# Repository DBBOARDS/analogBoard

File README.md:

# analogBoard
These are the Eagle files for the Analog Board

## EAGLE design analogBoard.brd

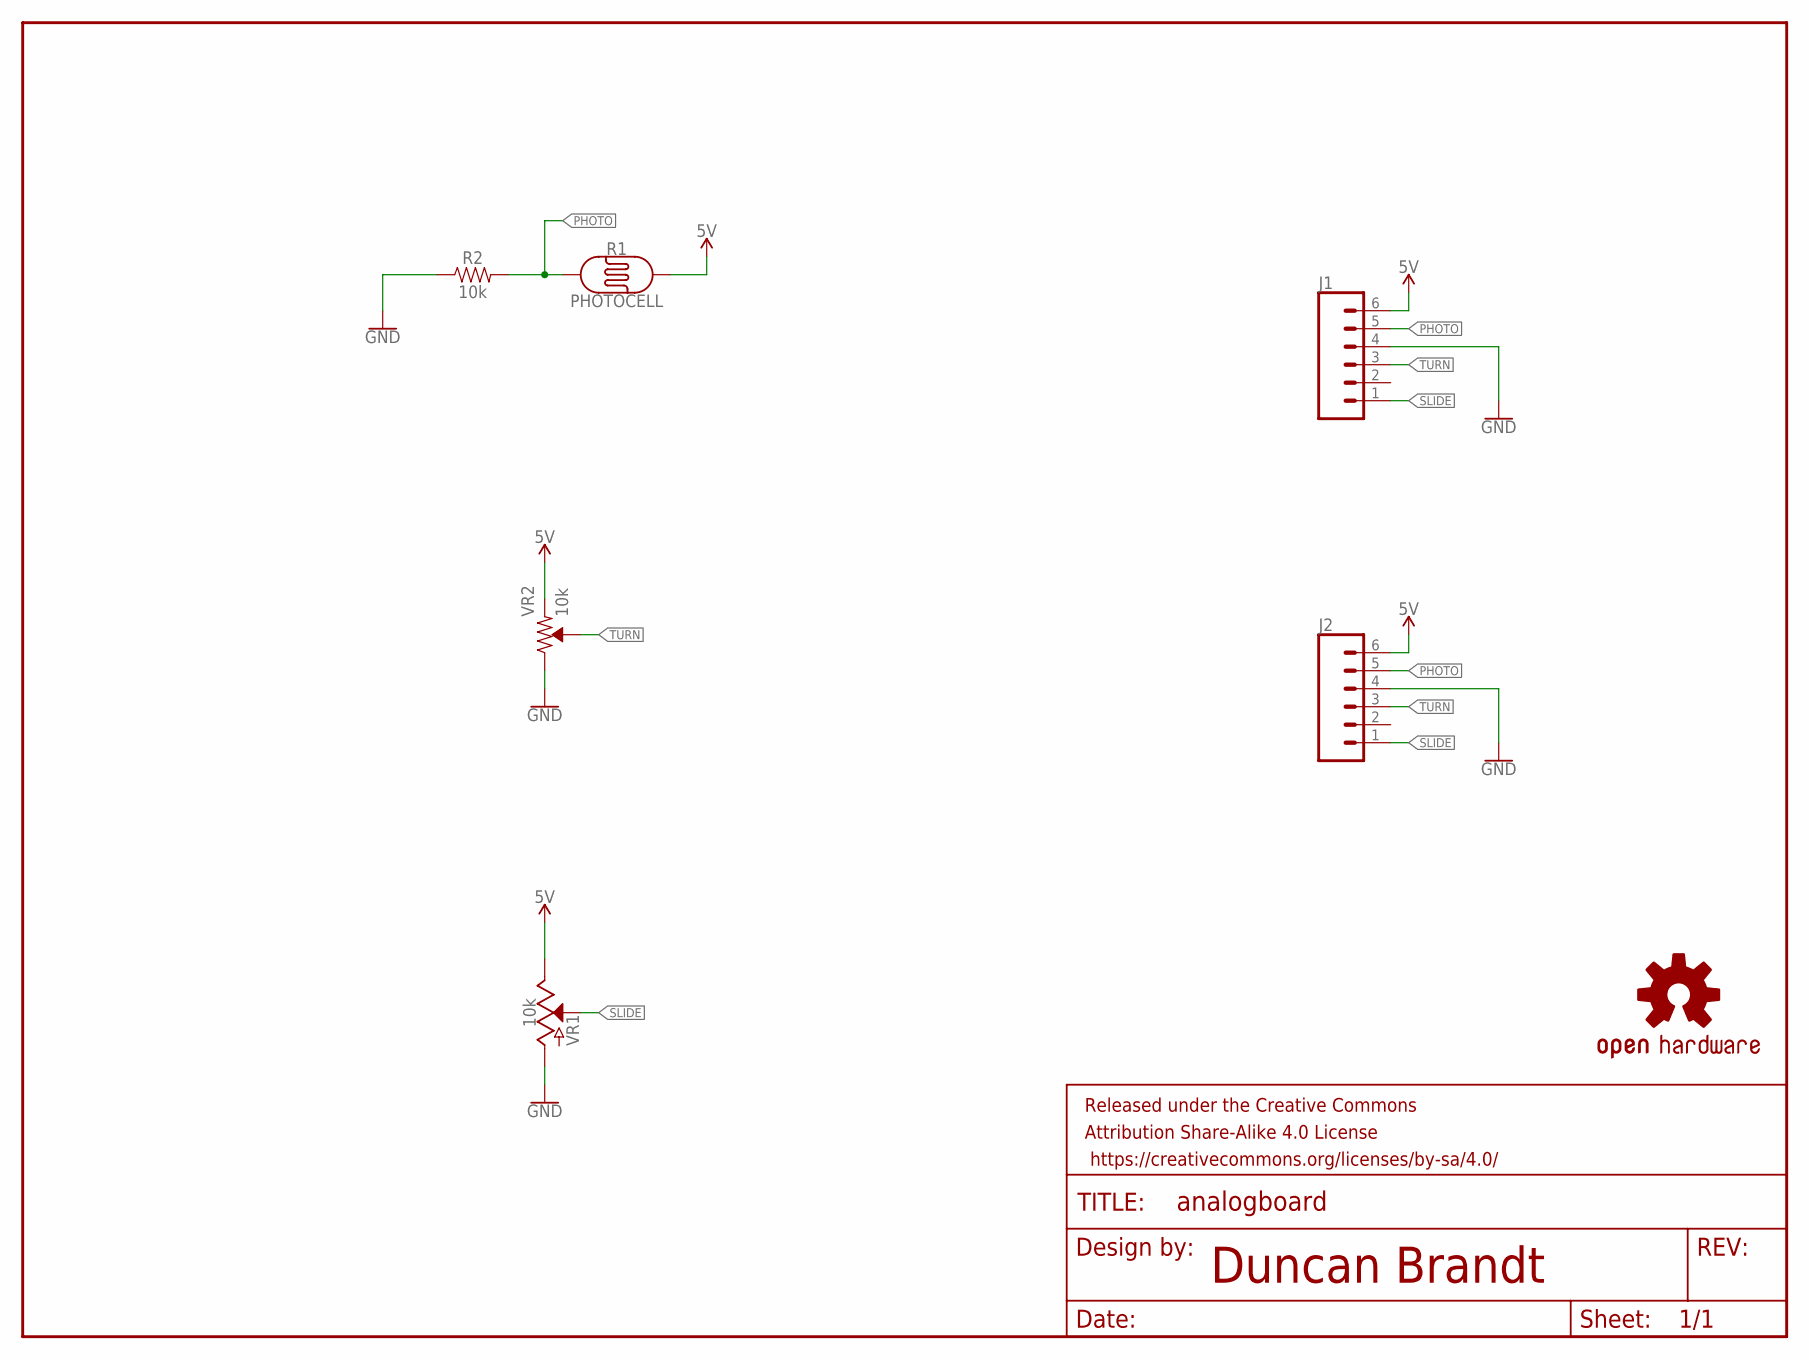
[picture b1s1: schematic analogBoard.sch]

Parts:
FRAME1: FRAME-LETTER; CREATIVE_COMMONS
J1, J2: CONN_06SILK_FEMALE_PTH; 1X06
LOGO1: OSHW-LOGOL; OSHW-LOGO-L
R1: PHOTOCELL
R2: 10k; 0603
VR1: 10k; SLIDER-SMALL
VR2: 10k; TRIMPOT-PTH-3386U

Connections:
5V: J1.6, J2.6, R1.2, VR2.1 (CCW)
GND: J1.4, J2.4, R2.1, VR1.BOTTOM (A), VR2.3 (CW)
PHOTO: J1.5, J2.5, R1.1, R2.2
SLIDE: J1.1, J2.1, VR1.WIPER (S)
TURN: J1.3, J2.3, VR2.2 (WIPER)
VIN: VR1.TOP (E)

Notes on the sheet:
Duncan Brandt

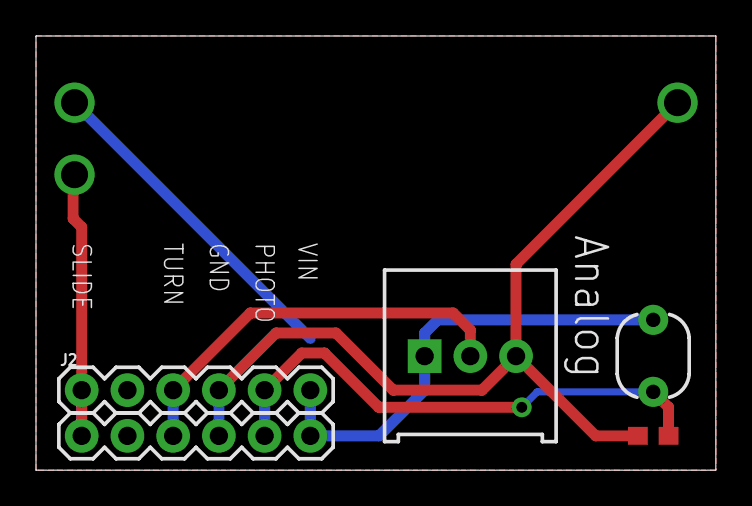
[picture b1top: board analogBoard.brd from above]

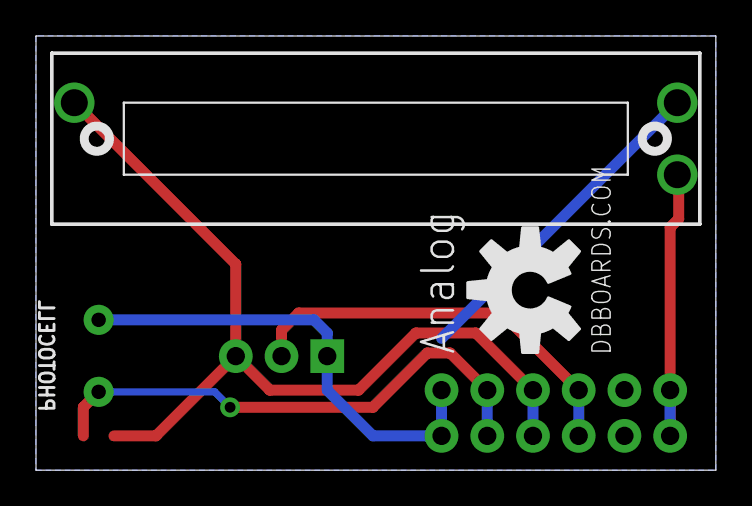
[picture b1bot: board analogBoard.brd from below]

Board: 2 copper layers, 37.8 x 24.1 mm, 8 parts (2 on the bottom side), 5 nets.

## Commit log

2018-02-20 Eagle Files

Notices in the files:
parts and their libraries:
DB-RES: Licensing: Creative Commons ShareAlike 4.0 International - https://creativecommons.org/licenses/by-sa/4.0
DB-SYMBOLS: Released under the Creative Commons Attribution Share-Alike 4.0 License
DB-SYMBOLS: https://creativecommons.org/licenses/by-sa/4.0
